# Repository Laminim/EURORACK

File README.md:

# ST MODULAR
_EURORACK DIY_

This repository was made to provide you with the neccessary information to source your parts and find their place on the PCB. There won´t be full build documentations available at any time in the future. 

If you have questions before or while building please join the [ST Modular Builders Group](https://www.facebook.com/groups/stmodular/) on Facebook. There you will also find additional information about the builds in the "units" section.

I also recommend to fully read the "Eurorack Soldering Guide" available above. It includes a step-by-step description how I solder DIY projects, a list of recommended soldering tools and some links that might be useful when jumping into Eurorack DIY.

All modules were developed as part of a hobby. All the knowledge of electronics and circuit board construction required to realise such projects was acquired through reading books, breadboarding and talking to other synthesiser hobbyists.

ST Modular itself does not sell products, but grants distribution licenses to third parties. In addition to selling PCBs, Panels and DIY kits, some partners of ST Modular also offer prefabricated modules. The availability of the PCBs and modules is solely in the hands of the dealers.

There are no PDF user manuals available for the modules. Functional descriptions and further details can be found on the respective module website. If there are any further questions, don't hesitate to ask in the ST Modular Builders Group on Facebook.
 
If you intend to build an ST MODULAR module, you should be able to solder components in the 0603 package. The PCBs are not necessarily designed to be easy to build, but are described by many builders as self-explanatory and intuitive to solder. Nevertheless, it is recommended that ST modular PCBs are only assembled by experienced builders.
 
The successful assembly, the safe power supply and the necessary calibration of the module are exclusively your responsibility. You are solely responsible for ensuring that the finished module does not damage other devices to which you connect it. You are responsible for any damage to other equipment. ST Modular is  not responsible if you injure yourself or others or damage your property or the property of others while building or using the circuit boards provided. No PCBs, complete kits or assembled modules will be available through st-modular.com in the future and no repairs will be offered or carried out.

For more information about the functionality of the modules please visit [www.st-modular.com](http://www.st-modular.com).

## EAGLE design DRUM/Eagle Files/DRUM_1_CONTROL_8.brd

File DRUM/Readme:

Released under cc-by-sa-3.0 license.

Resources:
https://github.com/pichenettes/eurorack
https://mutable-instruments.net/modules/peaks

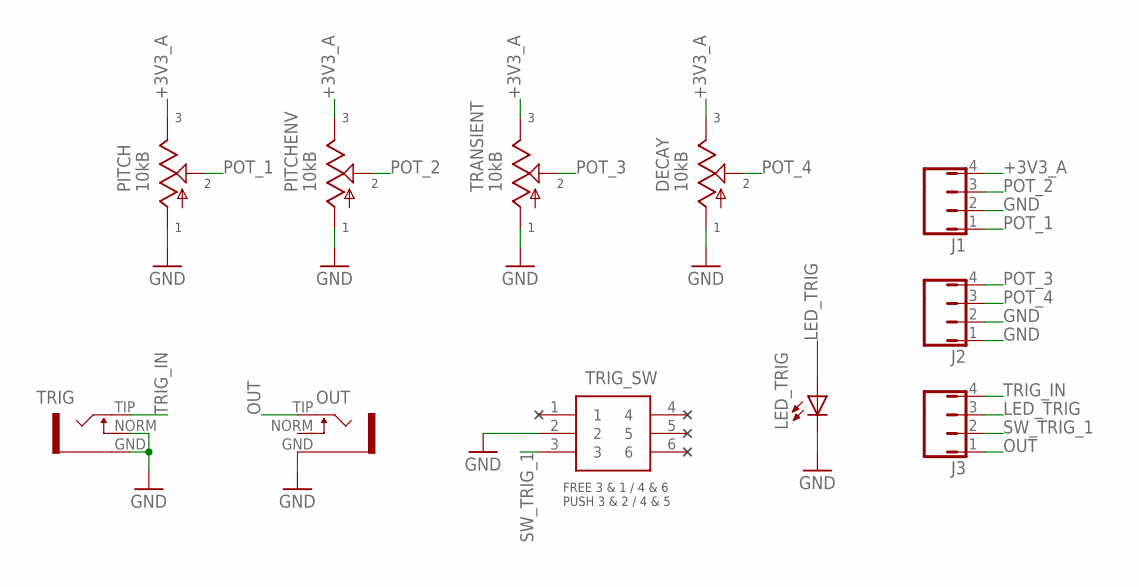
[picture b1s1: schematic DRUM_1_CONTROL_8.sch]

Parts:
DECAY: 10kB; 9MM_SNAP-IN_POT
J1, J2, J3: 1x4 FEMALE HEADER; JMP/4P/SIP
LED_TRIG: LEDS3MM; LED3MM
OUT: THONKICONN; INSTRUO_S_JACK_SMALL2
PITCH: 10kB; 9MM_SNAP-IN_POT
PITCHENV: 10kB; 9MM_SNAP-IN_POT
TRANSIENT: 10kB; 9MM_SNAP-IN_POT
TRIG: THONKICONN; INSTRUO_S_JACK_SMALL2
TRIG_SW: GPBS-800L 8MM MOMENTARY; GPBS800L

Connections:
+3V3_A: DECAY.3 (E), J1.4, PITCH.3 (E), PITCHENV.3 (E), TRANSIENT.3 (E)
GND: DECAY.1 (A), J1.2, J2.1, J2.2, LED_TRIG.K (C), OUT.GND, PITCH.1 (A), PITCHENV.1 (A), TRANSIENT.1 (A), TRIG.GND, TRIG.NORM, TRIG_SW.2
LED_TRIG: J3.3, LED_TRIG.A
OUT: J3.1, OUT.TIP
POT_1: J1.1, PITCH.2 (S)
POT_2: J1.3, PITCHENV.2 (S)
POT_3: J2.4, TRANSIENT.2 (S)
POT_4: DECAY.2 (S), J2.3
SW_TRIG_1: J3.2, TRIG_SW.3
TRIG_IN: J3.4, TRIG.TIP

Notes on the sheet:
FREE 3 & 1 / 4 & 6 PUSH 3 & 2 / 4 & 5

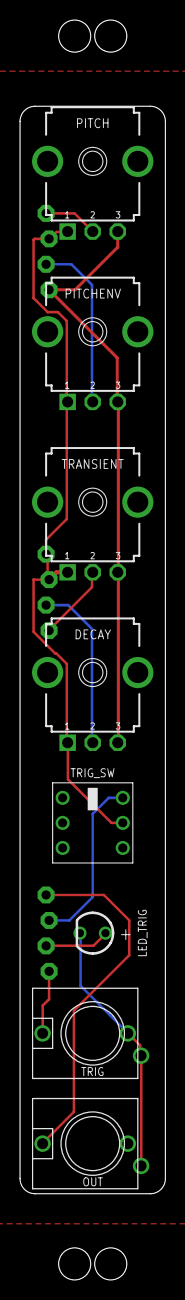
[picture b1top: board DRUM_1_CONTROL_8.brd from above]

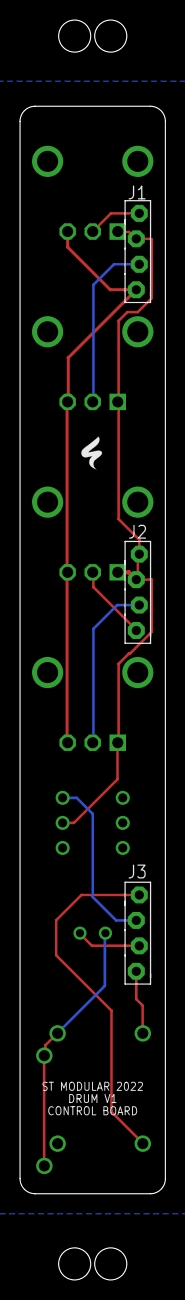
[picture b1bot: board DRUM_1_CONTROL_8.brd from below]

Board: 2 copper layers, 14.5 x 125.7 mm, 11 parts (3 on the bottom side), 10 nets.

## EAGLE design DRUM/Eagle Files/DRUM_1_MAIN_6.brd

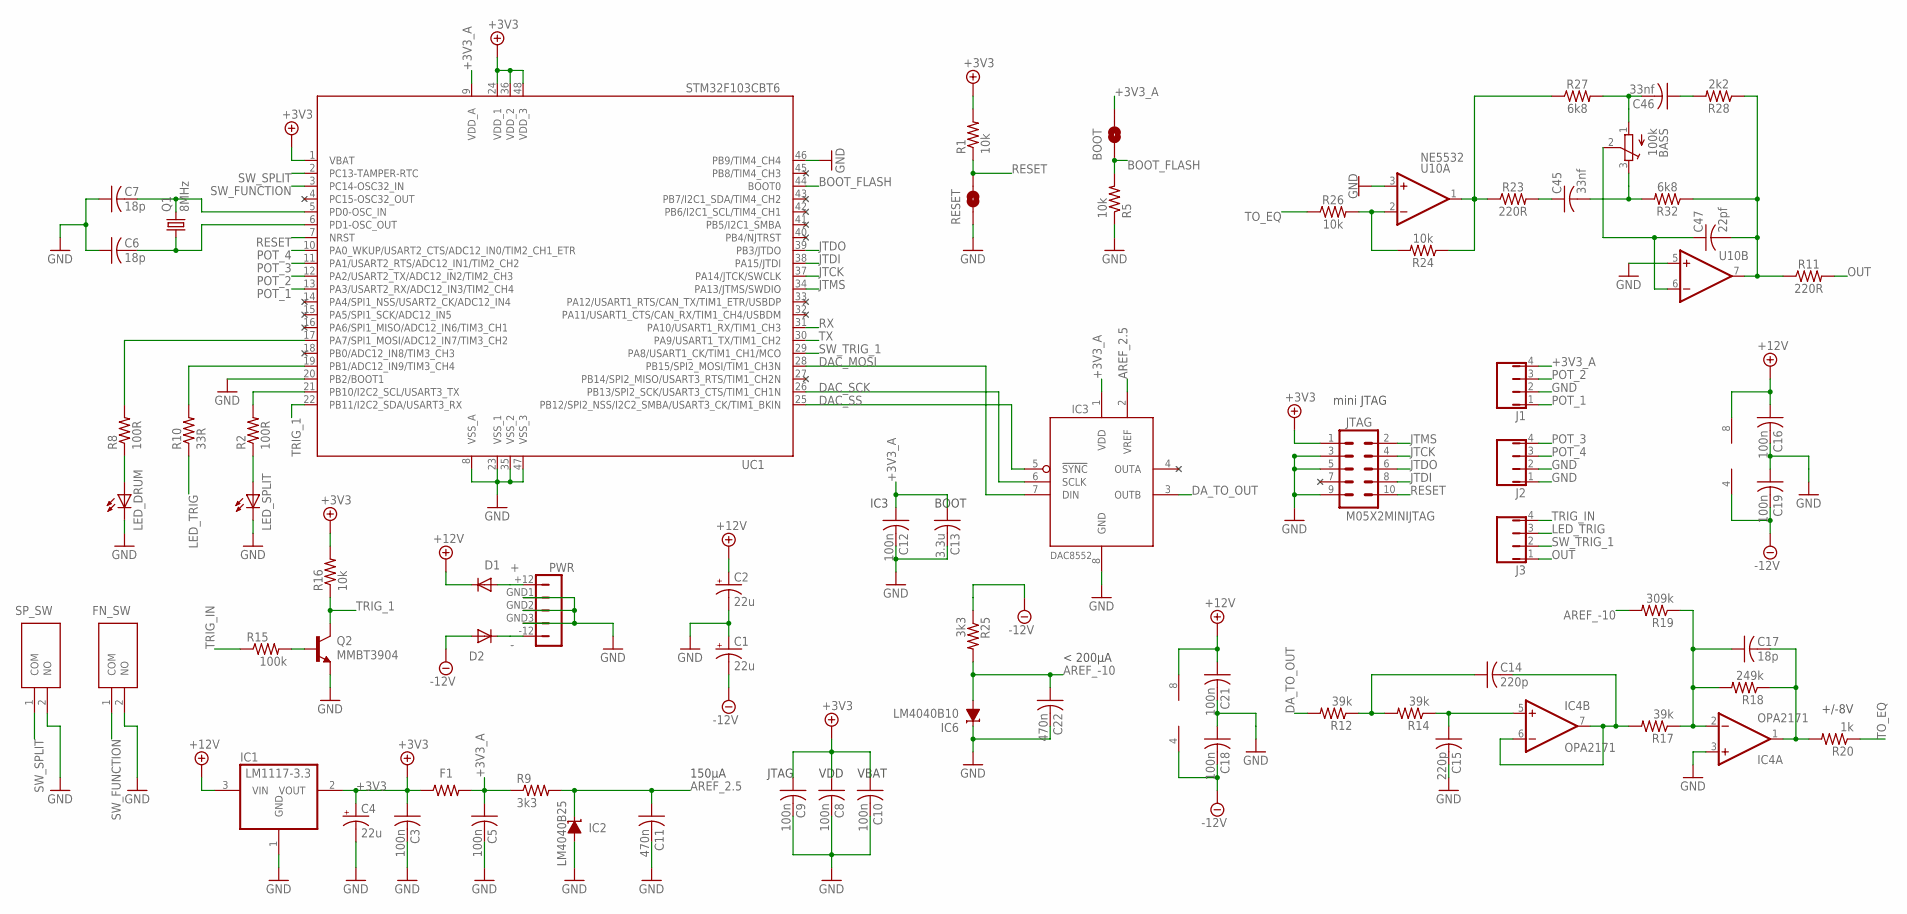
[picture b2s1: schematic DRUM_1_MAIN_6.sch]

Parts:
BASS: 100k; ADAFRUIT_TC33X
BOOT: BOOT; SMT-JUMPER_2_NO_SILK
C1, C2, C4: 22u; PANASONIC_C
C3, C5, C8, C9, C10, C12, C16, C18, C19, C21: 100n; C0603
C6, C7, C17: 18p; C0603
C11, C22: 470n; C0603
C13: 3.3u; C0805K
C14, C15: 220p; C0603
C45, C46: 33nf; C0603
C47: 22pf; C0603
D1, D2: 1N5819HW; PNS40010ER_SOD123W
F1: 742792693; R0603
FN_SW: PTS636_SM25_SMTR_LFS C778169; PTS636SM25SMTRLFS
IC1: LM1117-3.3; SOT223
IC2: LM4040B25; DBZ_R-PDSO-G3
IC3: DAC8552; MSOP-8
IC4: OPA2171; SO08
IC6: LM4040B10; DBZ_R-PDSO-G3
J1, J2, J3: 1x4 FEMALE HEADER; JMP/4P/SIP
JTAG: M05X2MINIJTAG; 2X5-1.27
LED_DRUM: LEDS0805; LED_0805A
LED_SPLIT: LEDS0805; LED_0805A
PWR: JMP/5P/DIP1X5_HEADER; JMP/5P/DIP
Q1: 8MHz; HC49UP
Q2: MMBT3904; SOT23-BEC
R1, R5, R16, R24, R26: 10k; R0603
R2, R8: 100R; R0603
R9, R25: 3k3; R0603
R10: 33R; R0603
R11, R23: 220R; R0603
R12, R14, R17: 39k; R0603
R15: 100k; R0603
R18: 249k; R0603
R19: 309k; R0603
R20: 1k; R0603
R27, R32: 6k8; R0603
R28: 2k2; R0603
RESET: RESET; SMT-JUMPER_2_NO_SILK
SP_SW: PTS636_SM25_SMTR_LFS C778169; PTS636SM25SMTRLFS
U10: NE5532; SO08
UC1: STM32F103CBT6; LQFP48

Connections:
+: D1.2 (A), PWR.+12
+3V3: C3.1, C4.+, C8.1, C9.1, C10.1, F1.1, IC1.2 (VOUT), JTAG.1, R1.2, R16.2, UC1.1 (VBAT), UC1.24 (VDD_1), UC1.36 (VDD_2), UC1.48 (VDD_3)
+3V3_A: BOOT.2, C5.1, C12.1, C13.1, F1.2, IC3.1 (VDD), J1.4, R9.1, UC1.9 (VDD_A)
+12V: C2.+, C16.1, C21.1, D1.1 (K), IC1.3 (VIN), IC4.8 (V+), U10.8 (V+)
-: D2.1 (K), PWR.-12
-12V: C1.-, C18.2, C19.2, D2.2 (A), IC4.4 (V-), R25.1, U10.4 (V-)
AREF_2.5: C11.1, IC2.1 (C), IC3.2 (VREF), R9.2
AREF_-10: C22.1, IC6.2 (A), R19.2, R25.2
BI_OUT: C17.2, IC4.1 (OUT), R18.1, R20.2
BOOT_FLASH: BOOT.1, R5.2, UC1.44 (BOOT0)
DAC_MOSI: IC3.7 (DIN), UC1.28 (PB15/SPI2_MOSI/TIM1_CH3N)
DAC_SCK: IC3.6 (SCLK), UC1.26 (PB13/SPI2_SCK/USART3_CTS/TIM1_CH1N)
DAC_SS: IC3.5 (!SYNC), UC1.25 (PB12/SPI2_NSS/I2C2_SMBA/USART3_CK/TIM1_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)
DA_TO_OUT: IC3.3 (OUTB), R12.2
F_CV: C17.1, IC4.2 (-IN), R17.1, R18.2, R19.1
GND: C1.+, C2.-, C3.2, C4.-, C5.2, C6.1, C7.1, C8.2, C9.2, C10.2, C11.2, C12.2, C13.2, C15.2, C16.2, C18.1, C19.1, C21.2, C22.2, FN_SW.2 (NO), IC1.1 (GND), IC2.2 (A), IC3.8 (GND), IC4.3 (+IN), IC6.1 (C), J1.2, J2.1, J2.2, JTAG.3, JTAG.5, JTAG.9, LED_DRUM.- (C), LED_SPLIT.- (C), PWR.GND1, PWR.GND2, PWR.GND3, Q2.E, R5.1, RESET.1, SP_SW.2 (NO), U10.3 (+IN), U10.5 (+IN), UC1.8 (VSS_A), UC1.20 (PB2/BOOT1), UC1.23 (VSS_1), UC1.35 (VSS_2), UC1.46 (PB9/TIM4_CH4), UC1.47 (VSS_3)
JTCK: JTAG.4, UC1.37 (PA14/JTCK/SWCLK)
JTDI: JTAG.8, UC1.38 (PA15/JTDI)
JTDO: JTAG.6, UC1.39 (PB3/JTDO)
JTMS: JTAG.2, UC1.34 (PA13/JTMS/SWDIO)
LED_TRIG: J3.3, R10.1
unnamed: R24.2, R26.2, U10.2 (-IN)
unnamed: LED_DRUM.+ (A), R8.1
unnamed: C7.2, Q1.2, UC1.5 (PD0-OSC_IN)
unnamed: C6.2, Q1.1, UC1.6 (PD1-OSC_OUT)
unnamed: R10.2, UC1.19 (PB1/ADC12_IN9/TIM3_CH4)
unnamed: R8.2, UC1.17 (PA7/SPI1_MOSI/ADC12_IN7/TIM3_CH2)
unnamed: Q2.B, R15.2
unnamed: LED_SPLIT.+ (A), R2.1
unnamed: R2.2, UC1.21 (PB10/I2C2_SCL/USART3_TX)
unnamed: C14.2, IC4.6 (-IN), IC4.7 (OUT), R17.2
unnamed: C15.1, IC4.5 (+IN), R14.1
unnamed: C14.1, R12.1, R14.2
unnamed: C47.2, R11.1, R28.1, R32.1, U10.7 (OUT)
unnamed: BASS.2, C47.1, U10.6 (-IN)
unnamed: R23.1, R24.1, R27.1, U10.1 (OUT)
unnamed: C45.1, R23.2
unnamed: BASS.1, C46.2, R27.2
unnamed: BASS.3, C45.2, R32.2
unnamed: C46.1, R28.2
OUT: J3.1, R11.2
POT_1: J1.1, UC1.13 (PA3/USART2_RX/ADC12_IN3/TIM2_CH4)
POT_2: J1.3, UC1.12 (PA2/USART2_TX/ADC12_IN2/TIM2_CH3)
POT_3: J2.4, UC1.11 (PA1/USART2_RTS/ADC12_IN1/TIM2_CH2)
POT_4: J2.3, UC1.10 (PA0_WKUP/USART2_CTS/ADC12_IN0/TIM2_CH1_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)
RESET: JTAG.10, R1.1, RESET.2, UC1.7 (NRST)
RX: UC1.31 (PA10/USART1_RX/TIM1_CH3)
SW_FUNCTION: FN_SW.1 (COM), UC1.3 (PC14-OSC32_IN)
SW_SPLIT: SP_SW.1 (COM), UC1.2 (PC13-TAMPER-RTC)
SW_TRIG_1: J3.2, UC1.29 (PA8/USART1_CK/TIM1_CH1/MCO)
TO_EQ: R20.1, R26.1
TRIG_1: Q2.C, R16.1, UC1.22 (PB11/I2C2_SDA/USART3_RX)
TRIG_IN: J3.4, R15.1
TX: UC1.30 (PA9/USART1_TX/TIM1_CH2)

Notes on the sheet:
mini JTAG
+/-8V
< 200µA
150µA
JTAG
VDD
VBAT
IC3
BOOT

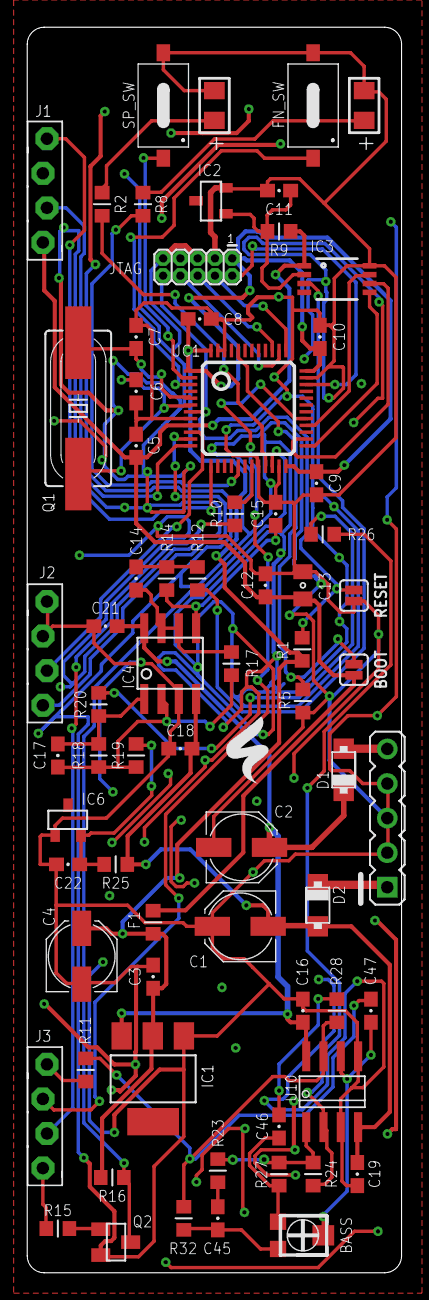
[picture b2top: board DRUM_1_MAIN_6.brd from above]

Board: 2 copper layers, 27.5 x 91.5 mm, 70 parts (0 on the bottom side), 52 nets.

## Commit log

2021-11-25 Create iBOM
2021-11-25 Rename Readme to Note
2021-11-25 Rename Note to Readme
2022-12-05 Create Readme
2022-12-20 Create TOUCH
2023-02-22 Create FIRMWARE
2023-04-24 Update STENCILS

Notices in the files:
parts and their libraries:
SparkFun-Jumpers: Licensing: Creative Commons ShareAlike 4.0 International - https://creativecommons.org/licenses/by-sa/4.0
